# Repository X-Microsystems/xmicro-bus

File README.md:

# XMICRO: A Modular 8-bit Microcomputer System
The XMICRO project began in 2017 as a hobby retrocomputer. Descending from a minimal 6502-based breadboard computer, the decision was made to create a platform which doesn't depend on any particular CPU architecture. In this way, many CPUs could be used for experimentation without the need to create an entire computer system around each one. The name XMICRO, meaning "variable microarchitecture", is a nod toward technology company names of the microcomputer revolution such as Zilog.

In 2020, the project was re-engineered from the ground up. This second generation of hardware improved the performance, reliability, and modularity of all parts of the system.

## Current State
The [XMICRO Bus Specification](Documentation/XMICRO%20Bus%20Specification.pdf) is not yet finalized, however many hardware components have been created which make up a functional 6502-based microcomputer. These include:
* [XMICRO-BP8](https://github.com/X-Microsystems/xmicro-bp8): 8-slot backplane
* [XMICRO-6502](https://github.com/X-Microsystems/xmicro-6502): W65C02 CPU card
* [XMICRO-MEMORY](https://github.com/X-Microsystems/xmicro-memory): 1MB RAM, 8kB ROM primary memory card
* [XMICRO-CF](https://github.com/X-Microsystems/xmicro-cf): CompactFlash storage and RTC card
* [XMICRO-SERIAL](https://github.com/X-Microsystems/xmicro-serial): Dual RS-232 and PS/2 communications card
* [XMICRO-VDP](https://github.com/X-Microsystems/xmicro-vdp): Yamaha V9958 video card

## Generation 2 Hardware Photos

## Generation 1 Hardware Photos

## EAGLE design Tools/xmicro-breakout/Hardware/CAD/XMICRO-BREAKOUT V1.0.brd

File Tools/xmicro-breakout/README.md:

# XMICRO-BREAKOUT
Card for breaking out all signals on the [XMICRO bus](https://github.com/x-microsystems/xmicro-bus) to 0.1" pin headers. Can be used with ribbon cables and the included breadboard module for prototyping on a functional system.

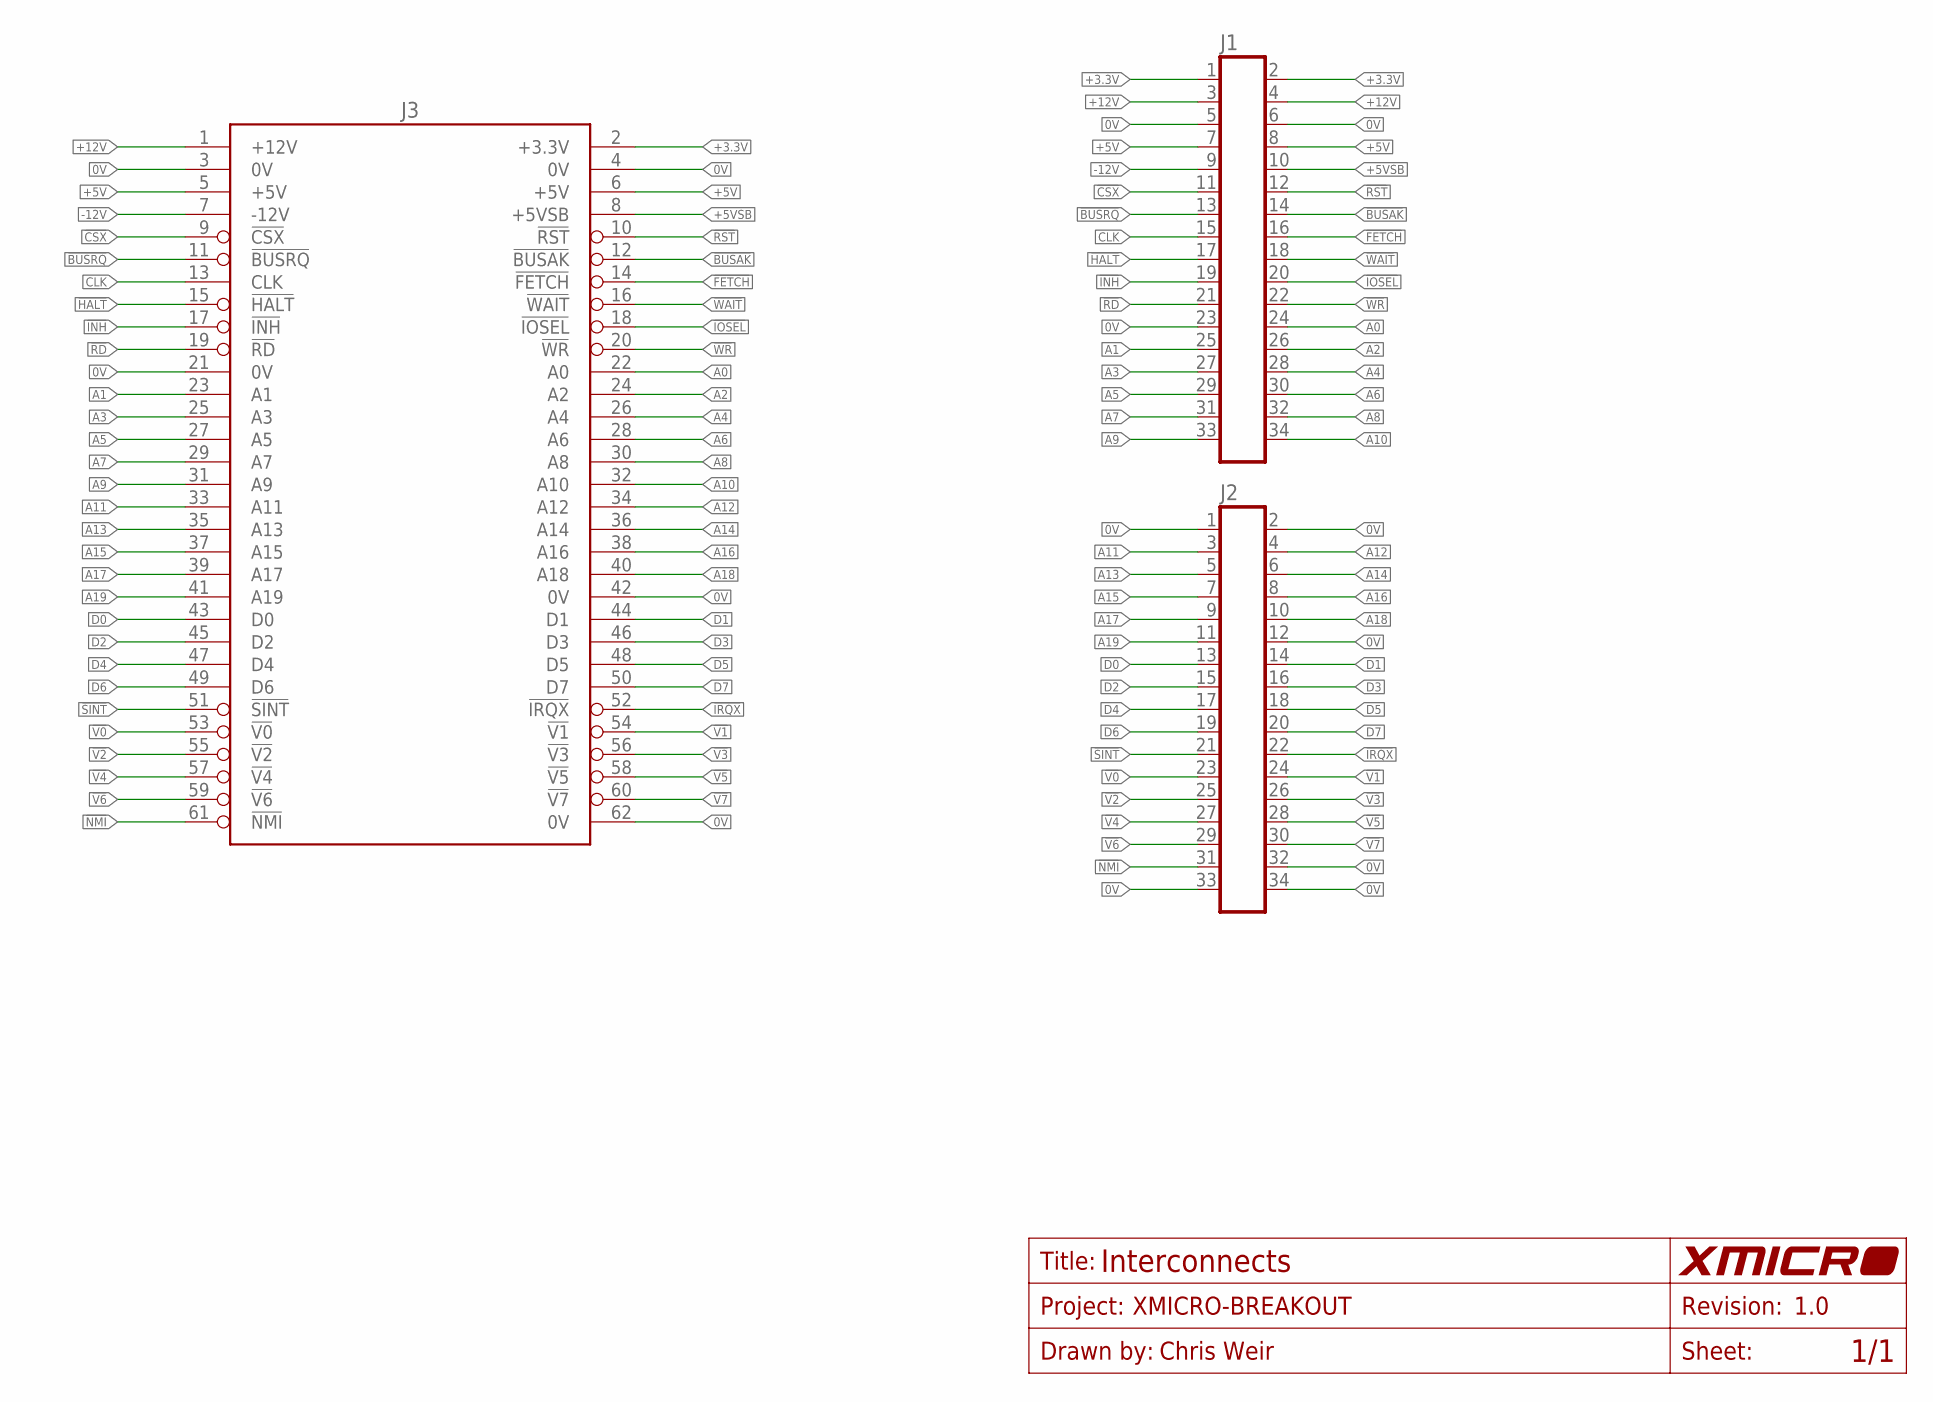
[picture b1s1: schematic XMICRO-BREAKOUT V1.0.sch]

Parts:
J1, J2: HDR-17X2; HDR-17X2S
J3: XMICRO-BUS-PHYSICAL-M; EDGE62M

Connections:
0V: J1.5, J1.6, J1.23, J2.1, J2.2, J2.12, J2.32, J2.33, J2.34, J3.3 (0V), J3.4 (0V), J3.21 (0V), J3.42 (0V), J3.62 (0V)
!BUSAK: J1.14, J3.12 (!BUSAK)
!BUSRQ: J1.13, J3.11 (!BUSRQ)
!CSX: J1.11, J3.9 (!CSX)
!FETCH: J1.16, J3.14 (!FETCH)
!HALT: J1.17, J3.15 (!HALT)
!INH: J1.19, J3.17 (!INH)
!IOSEL: J1.20, J3.18 (!IOSEL)
!IRQX: J2.22, J3.52 (!IRQX)
!NMI: J2.31, J3.61 (!NMI)
!RD: J1.21, J3.19 (!RD)
!RST: J1.12, J3.10 (!RST)
!SINT: J2.21, J3.51 (!SINT)
!V0: J2.23, J3.53 (!V0)
!V1: J2.24, J3.54 (!V1)
!V2: J2.25, J3.55 (!V2)
!V3: J2.26, J3.56 (!V3)
!V4: J2.27, J3.57 (!V4)
!V5: J2.28, J3.58 (!V5)
!V6: J2.29, J3.59 (!V6)
!V7: J2.30, J3.60 (!V7)
!WAIT: J1.18, J3.16 (!WAIT)
!WR: J1.22, J3.20 (!WR)
+3.3V: J1.1, J1.2, J3.2 (+3.3V)
+5V: J1.7, J1.8, J3.5 (+5V), J3.6 (+5V)
+5VSB: J1.10, J3.8 (+5VSB)
+12V: J1.3, J1.4, J3.1 (+12V)
-12V: J1.9, J3.7 (-12V)
A0: J1.24, J3.22 (A0)
A1: J1.25, J3.23 (A1)
A2: J1.26, J3.24 (A2)
A3: J1.27, J3.25 (A3)
A4: J1.28, J3.26 (A4)
A5: J1.29, J3.27 (A5)
A6: J1.30, J3.28 (A6)
A7: J1.31, J3.29 (A7)
A8: J1.32, J3.30 (A8)
A9: J1.33, J3.31 (A9)
A10: J1.34, J3.32 (A10)
A11: J2.3, J3.33 (A11)
A12: J2.4, J3.34 (A12)
A13: J2.5, J3.35 (A13)
A14: J2.6, J3.36 (A14)
A15: J2.7, J3.37 (A15)
A16: J2.8, J3.38 (A16)
A17: J2.9, J3.39 (A17)
A18: J2.10, J3.40 (A18)
A19: J2.11, J3.41 (A19)
CLK: J1.15, J3.13 (CLK)
D0: J2.13, J3.43 (D0)
D1: J2.14, J3.44 (D1)
D2: J2.15, J3.45 (D2)
D3: J2.16, J3.46 (D3)
D4: J2.17, J3.47 (D4)
D5: J2.18, J3.48 (D5)
D6: J2.19, J3.49 (D6)
D7: J2.20, J3.50 (D7)

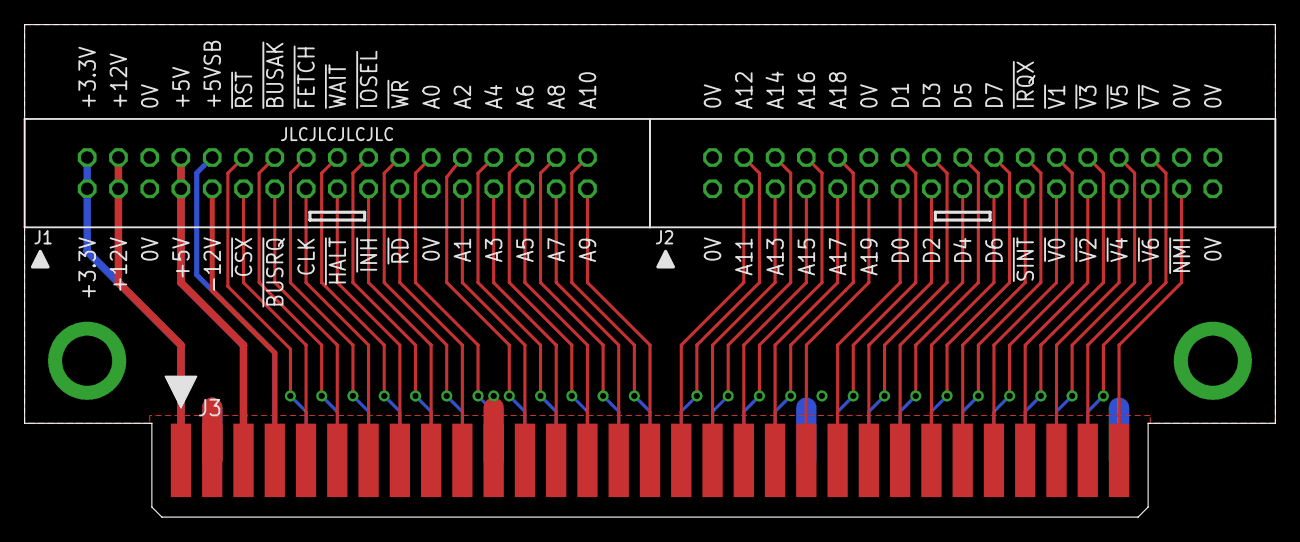
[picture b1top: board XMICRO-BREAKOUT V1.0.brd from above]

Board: 2 copper layers, 101.6 x 40.0 mm, 3 parts (0 on the bottom side), 57 nets.

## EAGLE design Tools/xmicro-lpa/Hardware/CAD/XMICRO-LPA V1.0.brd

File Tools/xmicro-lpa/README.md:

# XMICRO-LPA

HP/Agilent logic analyzer adapter for the [XMICRO bus](https://github.com/x-microsystems/xmicro-bus). Breaks out all signals to high-density Mictor connectors.

[Datasheet](Documentation/XMICRO-LPA.pdf)

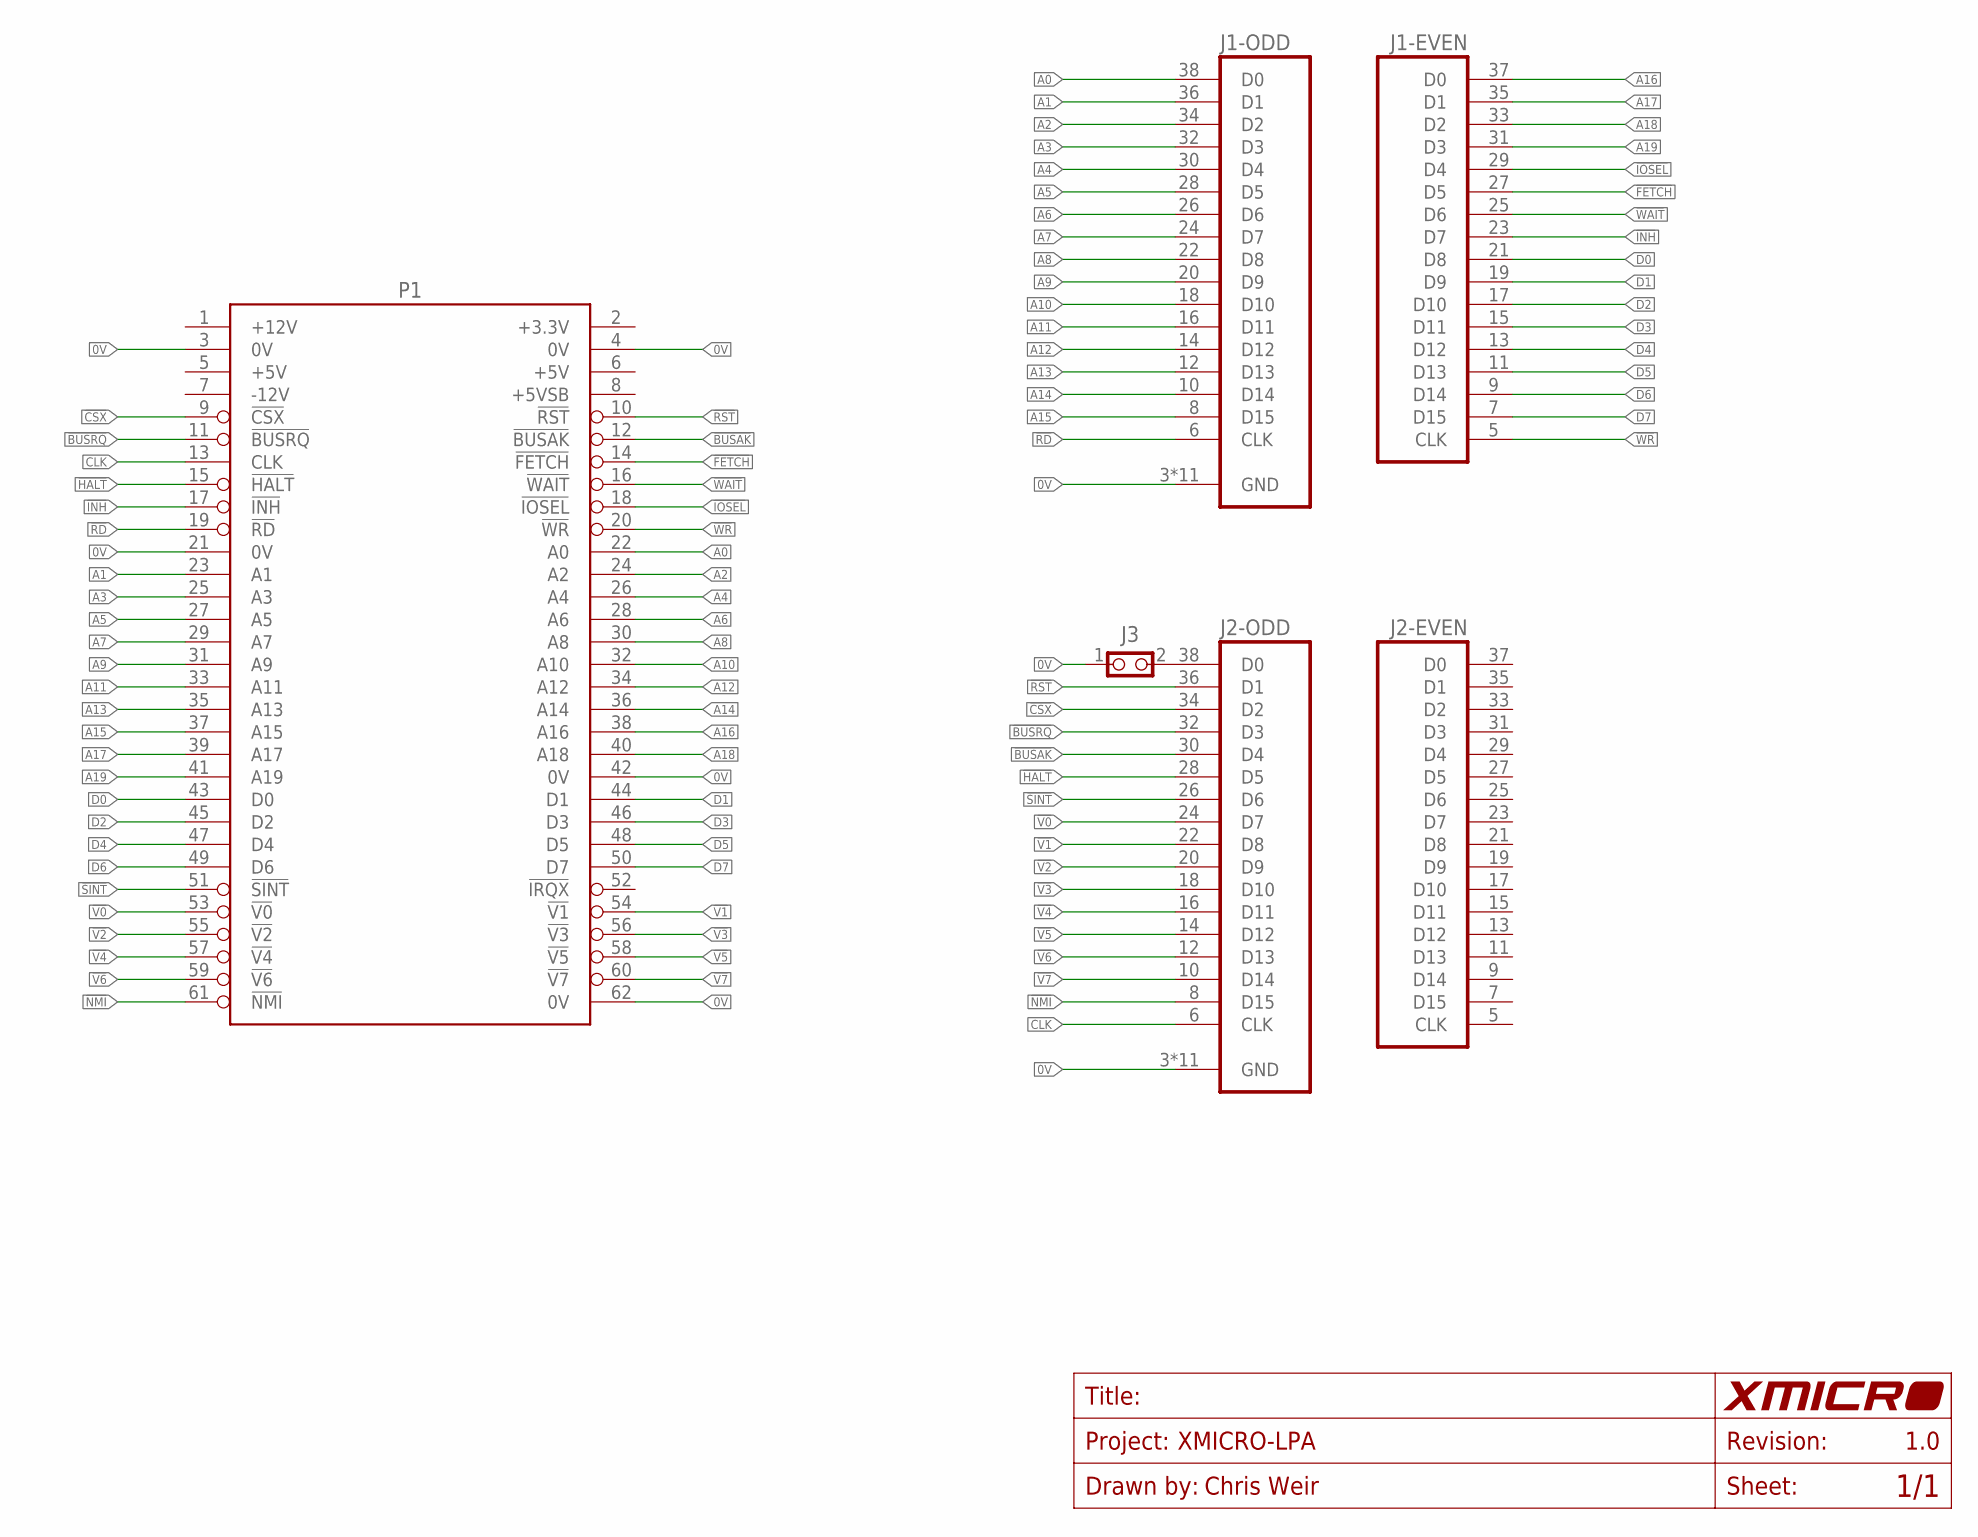
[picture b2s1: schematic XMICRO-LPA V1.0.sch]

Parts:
J1, J2: LA-34MEB; 5767089-1B
J3: 1X2-THRU; 1X2
P1: XMICRO-BUS-PHYSICAL-M; EDGE62M

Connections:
0V: J1.3 (GND), J1.G1 (GND), J1.G2 (GND), J1.G3 (GND), J1.G4 (GND), J1.G5 (GND), J1.G6 (GND), J1.G7 (GND), J1.G8 (GND), J1.G9 (GND), J1.G10 (GND), J2.3 (GND), J2.G1 (GND), J2.G2 (GND), J2.G3 (GND), J2.G4 (GND), J2.G5 (GND), J2.G6 (GND), J2.G7 (GND), J2.G8 (GND), J2.G9 (GND), J2.G10 (GND), J3.1, P1.3 (0V), P1.4 (0V), P1.21 (0V), P1.42 (0V), P1.62 (0V)
!BUSAK: J2.30 (D4), P1.12 (!BUSAK)
!BUSRQ: J2.32 (D3), P1.11 (!BUSRQ)
!CSX: J2.34 (D2), P1.9 (!CSX)
!FETCH: J1.27 (D5), P1.14 (!FETCH)
!HALT: J2.28 (D5), P1.15 (!HALT)
!INH: J1.23 (D7), P1.17 (!INH)
!IOSEL: J1.29 (D4), P1.18 (!IOSEL)
!NMI: J2.8 (D15), P1.61 (!NMI)
!RD: J1.6 (CLK), P1.19 (!RD)
!RST: J2.36 (D1), P1.10 (!RST)
!SINT: J2.26 (D6), P1.51 (!SINT)
!V0: J2.24 (D7), P1.53 (!V0)
!V1: J2.22 (D8), P1.54 (!V1)
!V2: J2.20 (D9), P1.55 (!V2)
!V3: J2.18 (D10), P1.56 (!V3)
!V4: J2.16 (D11), P1.57 (!V4)
!V5: J2.14 (D12), P1.58 (!V5)
!V6: J2.12 (D13), P1.59 (!V6)
!V7: J2.10 (D14), P1.60 (!V7)
!WAIT: J1.25 (D6), P1.16 (!WAIT)
!WR: J1.5 (CLK), P1.20 (!WR)
A0: J1.38 (D0), P1.22 (A0)
A1: J1.36 (D1), P1.23 (A1)
A2: J1.34 (D2), P1.24 (A2)
A3: J1.32 (D3), P1.25 (A3)
A4: J1.30 (D4), P1.26 (A4)
A5: J1.28 (D5), P1.27 (A5)
A6: J1.26 (D6), P1.28 (A6)
A7: J1.24 (D7), P1.29 (A7)
A8: J1.22 (D8), P1.30 (A8)
A9: J1.20 (D9), P1.31 (A9)
A10: J1.18 (D10), P1.32 (A10)
A11: J1.16 (D11), P1.33 (A11)
A12: J1.14 (D12), P1.34 (A12)
A13: J1.12 (D13), P1.35 (A13)
A14: J1.10 (D14), P1.36 (A14)
A15: J1.8 (D15), P1.37 (A15)
A16: J1.37 (D0), P1.38 (A16)
A17: J1.35 (D1), P1.39 (A17)
A18: J1.33 (D2), P1.40 (A18)
A19: J1.31 (D3), P1.41 (A19)
CLK: J2.6 (CLK), P1.13 (CLK)
D0: J1.21 (D8), P1.43 (D0)
D1: J1.19 (D9), P1.44 (D1)
D2: J1.17 (D10), P1.45 (D2)
D3: J1.15 (D11), P1.46 (D3)
D4: J1.13 (D12), P1.47 (D4)
D5: J1.11 (D13), P1.48 (D5)
D6: J1.9 (D14), P1.49 (D6)
D7: J1.7 (D15), P1.50 (D7)
unnamed: J2.38 (D0), J3.2

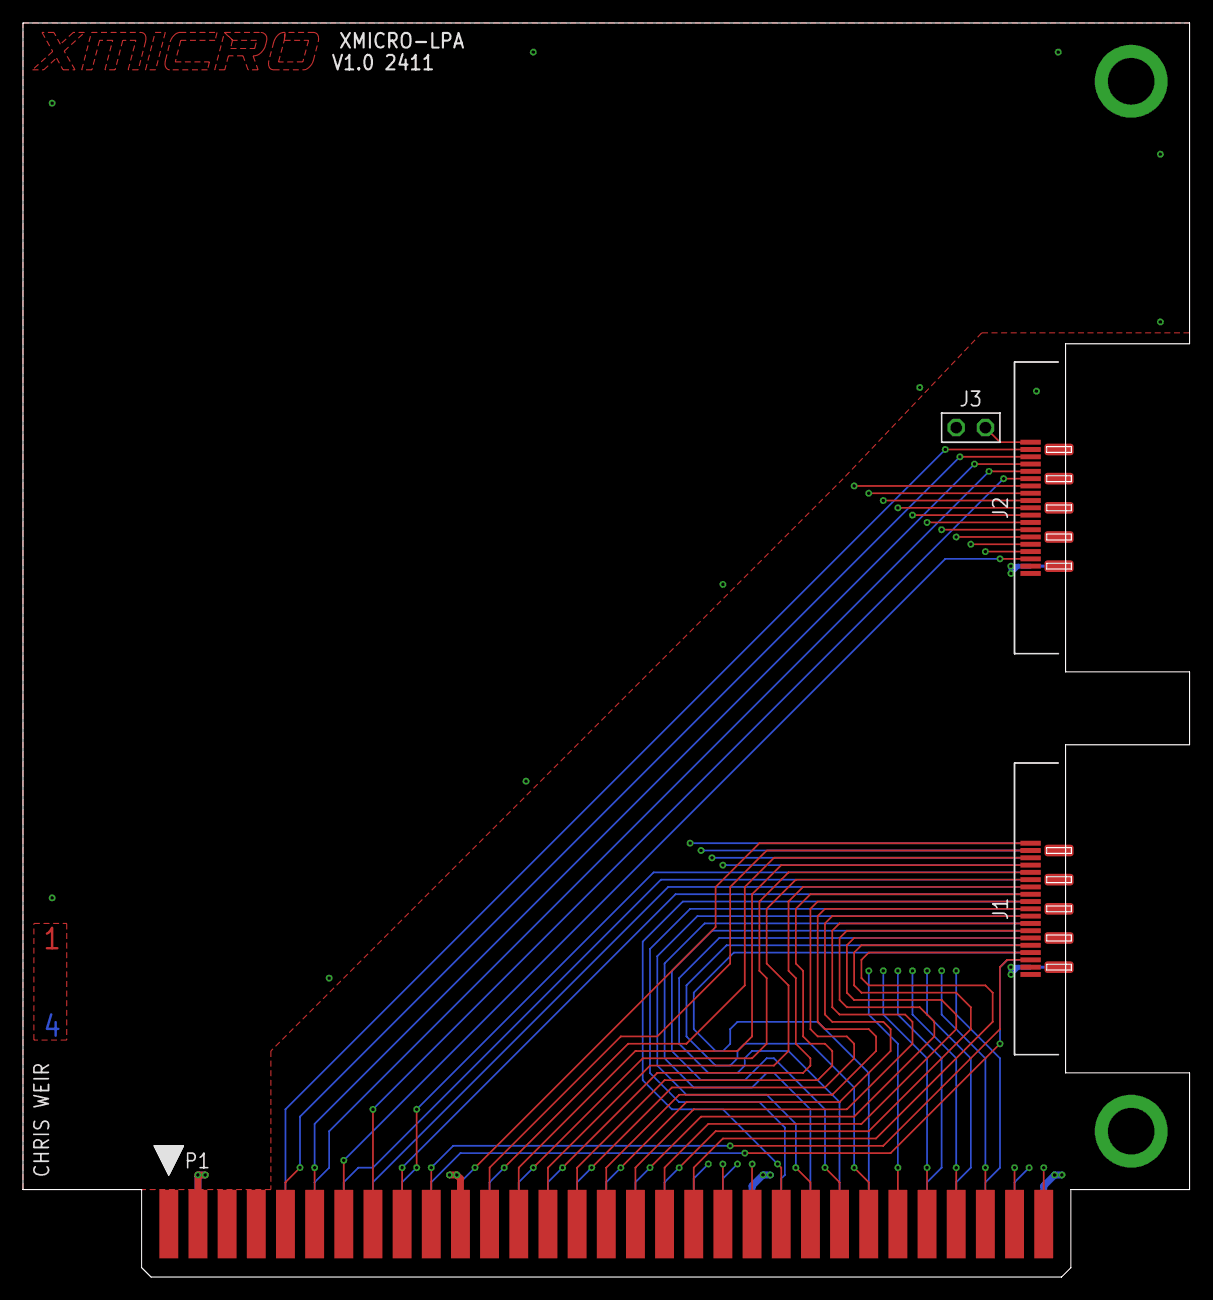
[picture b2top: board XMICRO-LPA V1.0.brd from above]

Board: 4 copper layers, 101.6 x 109.2 mm, 4 parts (0 on the bottom side), 52 nets.

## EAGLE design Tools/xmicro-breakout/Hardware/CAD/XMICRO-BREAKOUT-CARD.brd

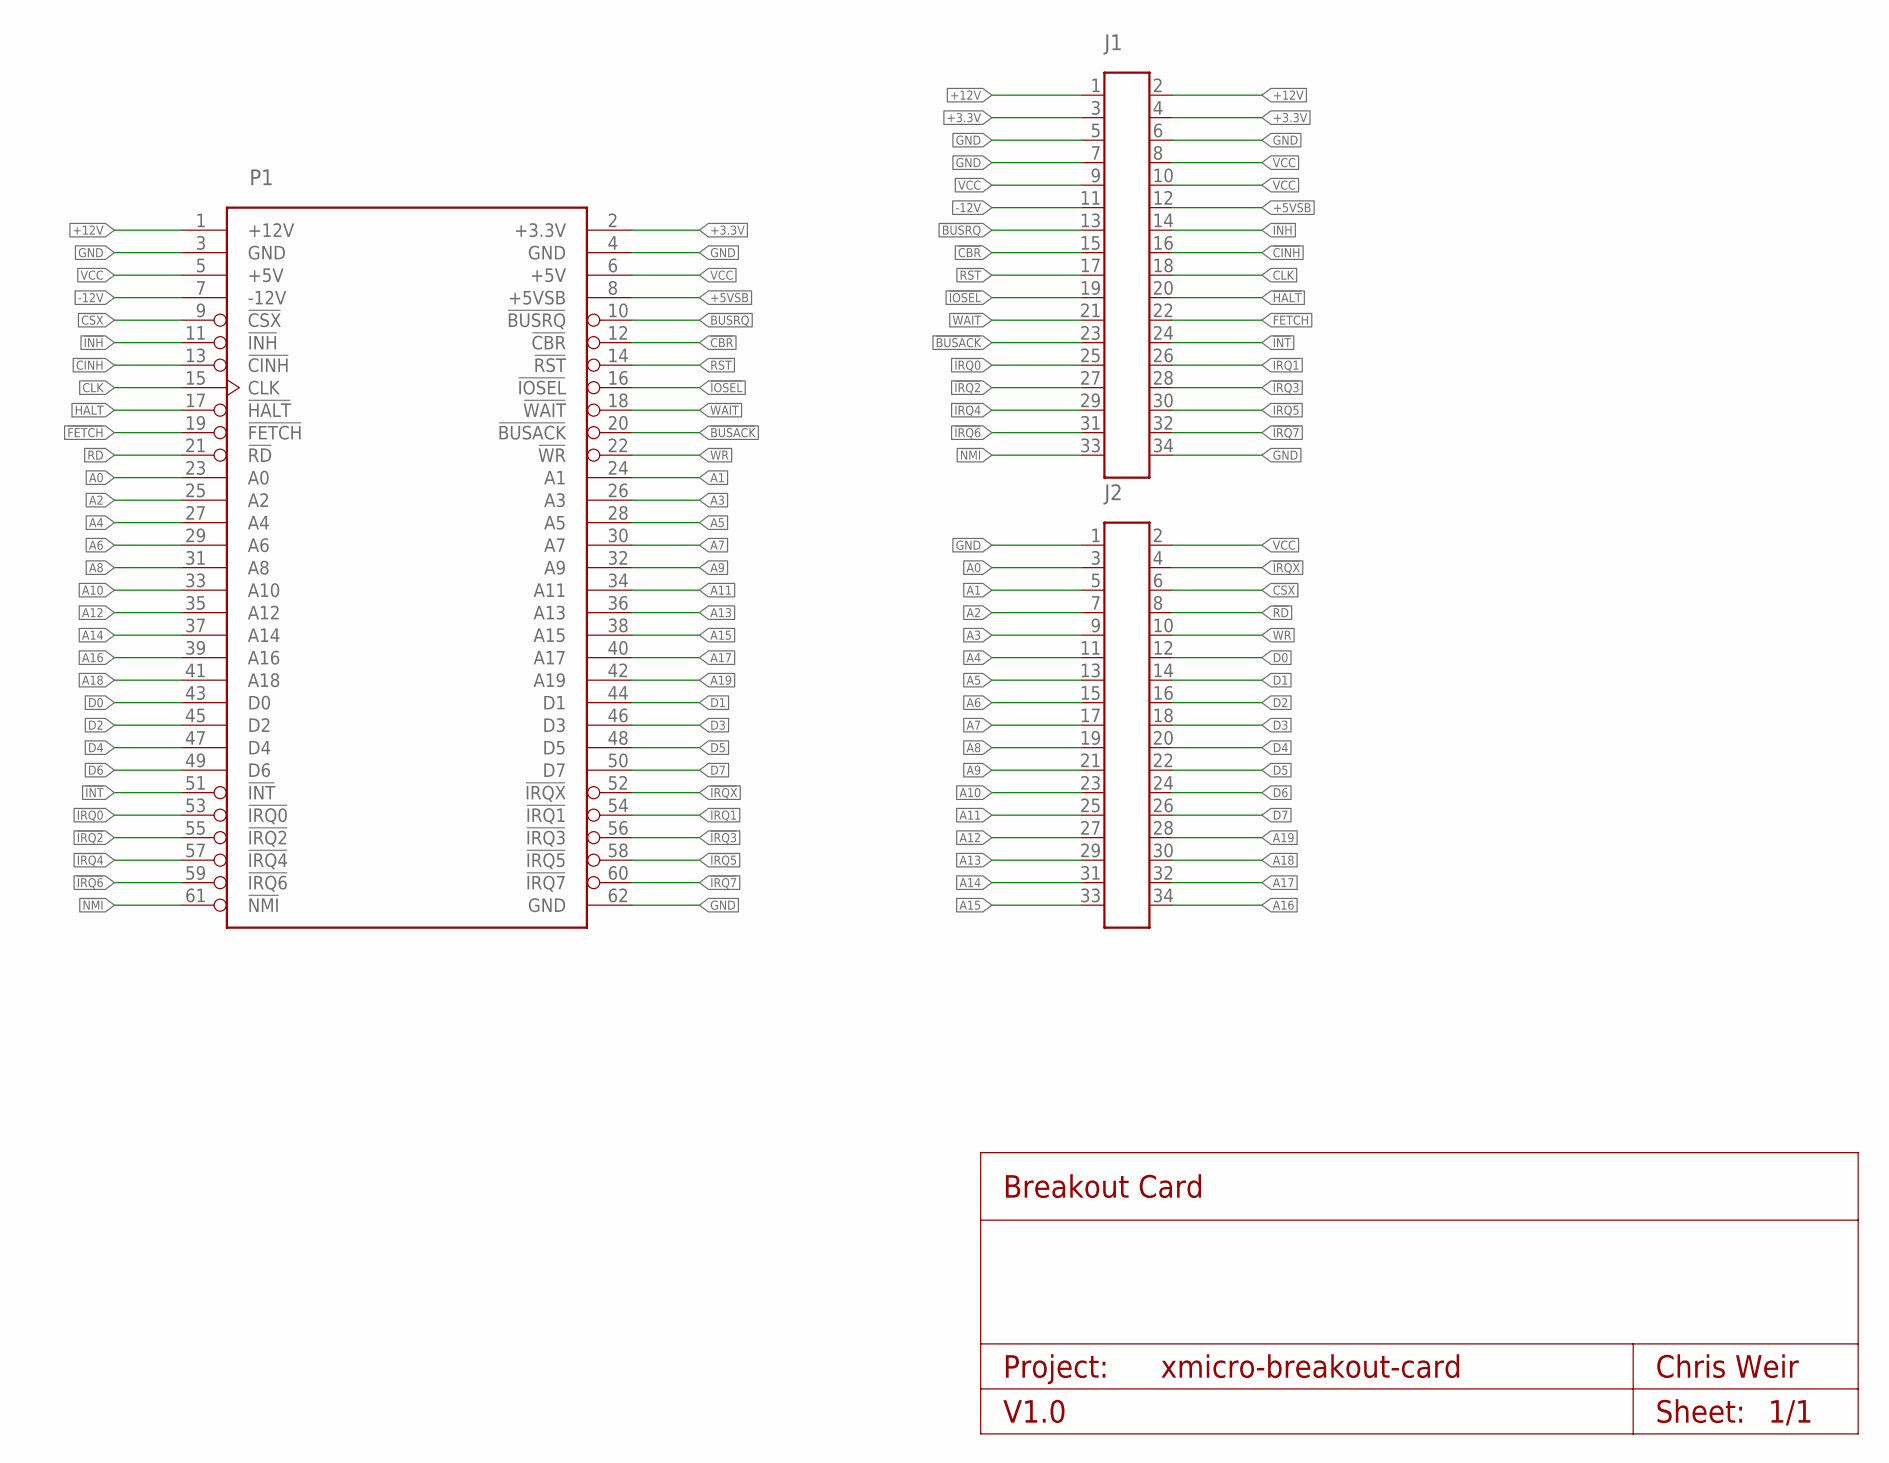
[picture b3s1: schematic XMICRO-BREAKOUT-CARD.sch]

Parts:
J1, J2: HDR-17X2; HDR-17X2S
P1: XMICRO-BUS-PHYSICAL-EDGE62M; EDGE62M

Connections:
!BUSACK: J1.23, P1.20 (!BUSACK)
!BUSRQ: J1.13, P1.10 (!BUSRQ)
!CBR: J1.15, P1.12 (!CBR)
!CINH: J1.16, P1.13 (!CINH)
!CSX: J2.6, P1.9 (!CSX)
!FETCH: J1.22, P1.19 (!FETCH)
!HALT: J1.20, P1.17 (!HALT)
!INH: J1.14, P1.11 (!INH)
!INT: J1.24, P1.51 (!INT)
!IOSEL: J1.19, P1.16 (!IOSEL)
!IRQ0: J1.25, P1.53 (!IRQ0)
!IRQ1: J1.26, P1.54 (!IRQ1)
!IRQ2: J1.27, P1.55 (!IRQ2)
!IRQ3: J1.28, P1.56 (!IRQ3)
!IRQ4: J1.29, P1.57 (!IRQ4)
!IRQ5: J1.30, P1.58 (!IRQ5)
!IRQ6: J1.31, P1.59 (!IRQ6)
!IRQ7: J1.32, P1.60 (!IRQ7)
!IRQX: J2.4, P1.52 (!IRQX)
!NMI: J1.33, P1.61 (!NMI)
!RD: J2.8, P1.21 (!RD)
!RST: J1.17, P1.14 (!RST)
!WAIT: J1.21, P1.18 (!WAIT)
!WR: J2.10, P1.22 (!WR)
+3.3V: J1.3, J1.4, P1.2 (+3.3V)
+5VSB: J1.12, P1.8 (+5VSB)
+12V: J1.1, J1.2, P1.1 (+12V)
-12V: J1.11, P1.7 (-12V)
A0: J2.3, P1.23 (A0)
A1: J2.5, P1.24 (A1)
A2: J2.7, P1.25 (A2)
A3: J2.9, P1.26 (A3)
A4: J2.11, P1.27 (A4)
A5: J2.13, P1.28 (A5)
A6: J2.15, P1.29 (A6)
A7: J2.17, P1.30 (A7)
A8: J2.19, P1.31 (A8)
A9: J2.21, P1.32 (A9)
A10: J2.23, P1.33 (A10)
A11: J2.25, P1.34 (A11)
A12: J2.27, P1.35 (A12)
A13: J2.29, P1.36 (A13)
A14: J2.31, P1.37 (A14)
A15: J2.33, P1.38 (A15)
A16: J2.34, P1.39 (A16)
A17: J2.32, P1.40 (A17)
A18: J2.30, P1.41 (A18)
A19: J2.28, P1.42 (A19)
CLK: J1.18, P1.15 (CLK)
D0: J2.12, P1.43 (D0)
D1: J2.14, P1.44 (D1)
D2: J2.16, P1.45 (D2)
D3: J2.18, P1.46 (D3)
D4: J2.20, P1.47 (D4)
D5: J2.22, P1.48 (D5)
D6: J2.24, P1.49 (D6)
D7: J2.26, P1.50 (D7)
GND: J1.5, J1.6, J1.7, J1.34, J2.1, P1.3 (GND), P1.4 (GND), P1.62 (GND)
VCC: J1.8, J1.9, J1.10, J2.2, P1.5 (+5V), P1.6 (+5V)

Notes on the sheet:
Breakout Card
Project:
V1.0
Chris Weir
Sheet:

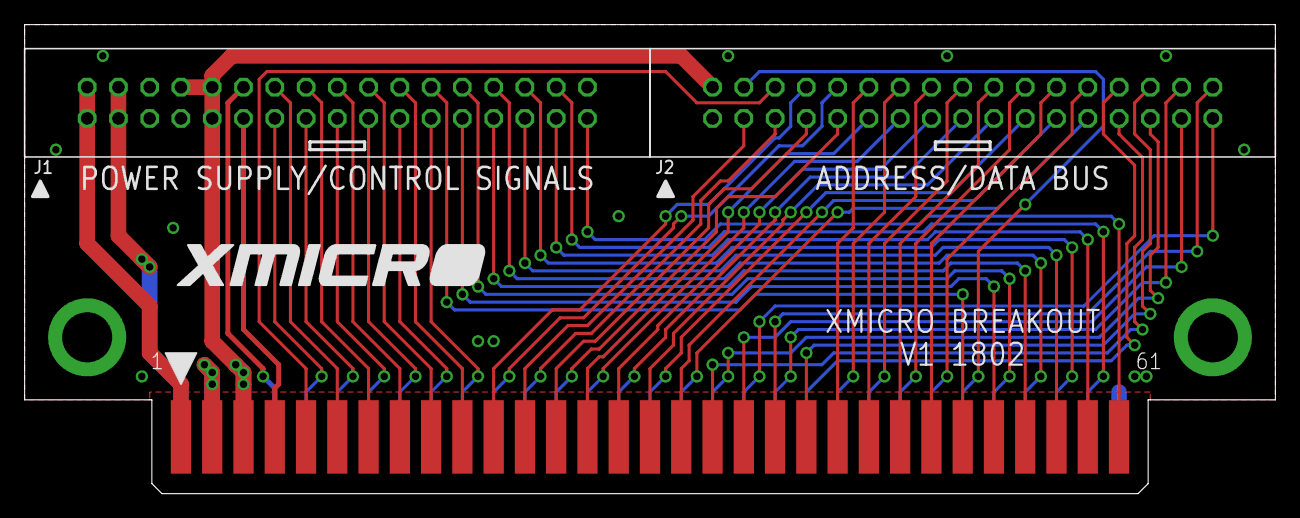
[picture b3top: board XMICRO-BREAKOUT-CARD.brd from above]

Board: 2 copper layers, 101.6 x 38.1 mm, 3 parts (0 on the bottom side), 59 nets.

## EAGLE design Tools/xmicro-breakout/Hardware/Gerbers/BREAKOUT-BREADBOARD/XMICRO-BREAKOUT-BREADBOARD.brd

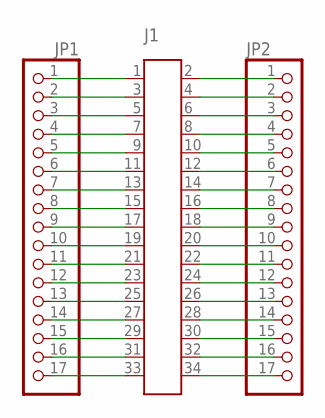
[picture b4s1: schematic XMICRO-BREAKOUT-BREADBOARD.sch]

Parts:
J1: HDR-17X2; HDR-17X2S
JP1, JP2: PINHD-1X17; 1X17

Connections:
unnamed: J1.1, JP1.1
unnamed: J1.3, JP1.2
unnamed: J1.5, JP1.3
unnamed: J1.7, JP1.4
unnamed: J1.9, JP1.5
unnamed: J1.11, JP1.6
unnamed: J1.13, JP1.7
unnamed: J1.15, JP1.8
unnamed: J1.17, JP1.9
unnamed: J1.19, JP1.10
unnamed: J1.21, JP1.11
unnamed: J1.23, JP1.12
unnamed: J1.25, JP1.13
unnamed: J1.27, JP1.14
unnamed: J1.29, JP1.15
unnamed: J1.31, JP1.16
unnamed: J1.33, JP1.17
unnamed: J1.2, JP2.1
unnamed: J1.4, JP2.2
unnamed: J1.6, JP2.3
unnamed: J1.8, JP2.4
unnamed: J1.10, JP2.5
unnamed: J1.12, JP2.6
unnamed: J1.14, JP2.7
unnamed: J1.16, JP2.8
unnamed: J1.18, JP2.9
unnamed: J1.20, JP2.10
unnamed: J1.22, JP2.11
unnamed: J1.24, JP2.12
unnamed: J1.26, JP2.13
unnamed: J1.28, JP2.14
unnamed: J1.30, JP2.15
unnamed: J1.32, JP2.16
unnamed: J1.34, JP2.17

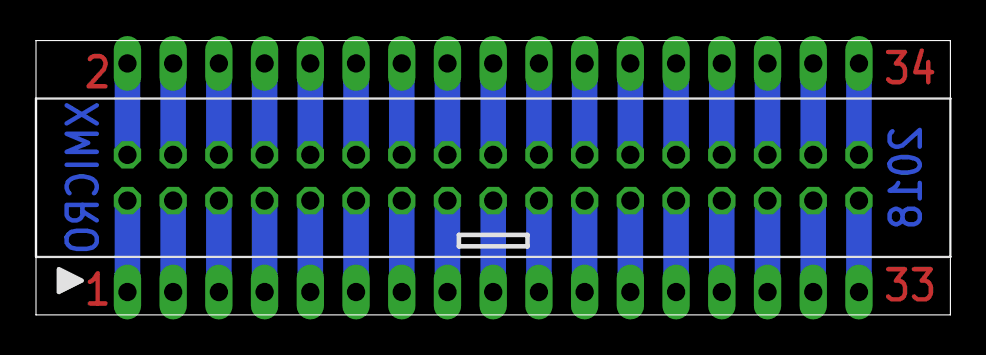
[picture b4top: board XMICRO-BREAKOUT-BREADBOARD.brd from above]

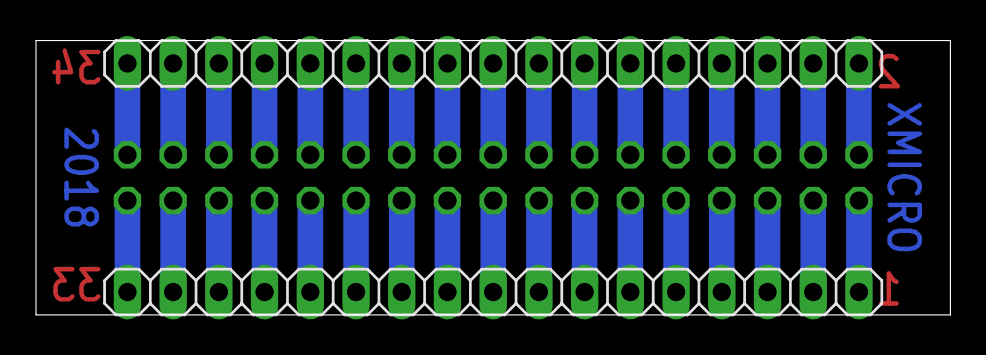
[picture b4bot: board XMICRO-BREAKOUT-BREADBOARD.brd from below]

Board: 2 copper layers, 50.8 x 15.2 mm, 3 parts (2 on the bottom side), 34 nets.

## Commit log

2018-08-16 Updated the name in the license
2018-10-07 Added dimensional drawings for cards
2018-10-08 Added backplane dimensions and updated the specification document
2018-10-08 Updated specification document and dimensional drawings
2018-10-22 Expended roadmap and moved it to a separate document
2018-11-19 Minor document updates
2018-11-30 Updated NMI signal and related DMA descriptions
2019-03-04 Updated physical dimensions (PCB rear edge to chassis)
2019-03-04 Updated pinout - Replaced CLKAUX with /IO
2019-03-04 Began work on timing diagrams
2019-03-04 Updaed the document to reflect recent changes
2019-03-07 Fixed dimensional drawings
2019-03-08 Fixed dimensional drawings and pinout diagram
2019-03-08 Updated PDF
2019-03-24 Moved bus tools into this repository.
2019-03-24 Fixed an issue with the XMICRO-EXT riser card.
2019-03-24 Changed IO signal name to IOSEL
2019-03-24 Added XMICRO-PROTO card to tools
2019-03-24 Fixed tools with new IOSEL signal
2019-03-24 Added a list of standard card IDs
2019-10-28 XMICRO-EXT: Modified connector footprint
2019-10-28 Bus Specification: Minor changes
2020-07-06 Updated specification
2020-07-09 Updating bus specification
2020-08-29 Updated READMEs and added images of the system
2020-08-29 Fixed link in README.md
2020-08-30 Added pictures and updated README.md
2020-10-22 Updated bus specification
2020-10-26 Updated to V0.4 - modified bus connector pinout
2020-12-16 Added timing diagrams
2021-01-02 Updated timing specs, changed physical drawings font
2021-02-07 Minor updates
2021-02-08 Changed bus connector pinout
2021-02-08 Removed references to NC signal pins
2021-02-09 Added license page
2021-03-02 Changed bus pinout
2021-05-01 Updated bus arbitration description and diagram
2021-05-16 Renamed INTS to SINT, various minor edits
2021-05-17 Various rewrites and clarifications
2022-02-01 Updated bus arbitration diagram
2022-05-11 Updated physical specifications for the XMICRO-CASE project
2022-09-07 Appendix A. Added new ID for XMICRO-CF
2024-09-14 Added XMICRO-LPA documentation and hardware
2024-09-14 Removed XMICRO-PROTO because small-run manufacturers refuse to make it
2024-09-14 Updated hardware tools to Gen 2
2024-09-29 Updated tool documentation
2024-09-29 Added template for datasheets
2024-09-30 Updated datasheet template
2025-08-05 Minor documentation improvements
2025-08-05 Updated Readme with Gen2 photos/information
